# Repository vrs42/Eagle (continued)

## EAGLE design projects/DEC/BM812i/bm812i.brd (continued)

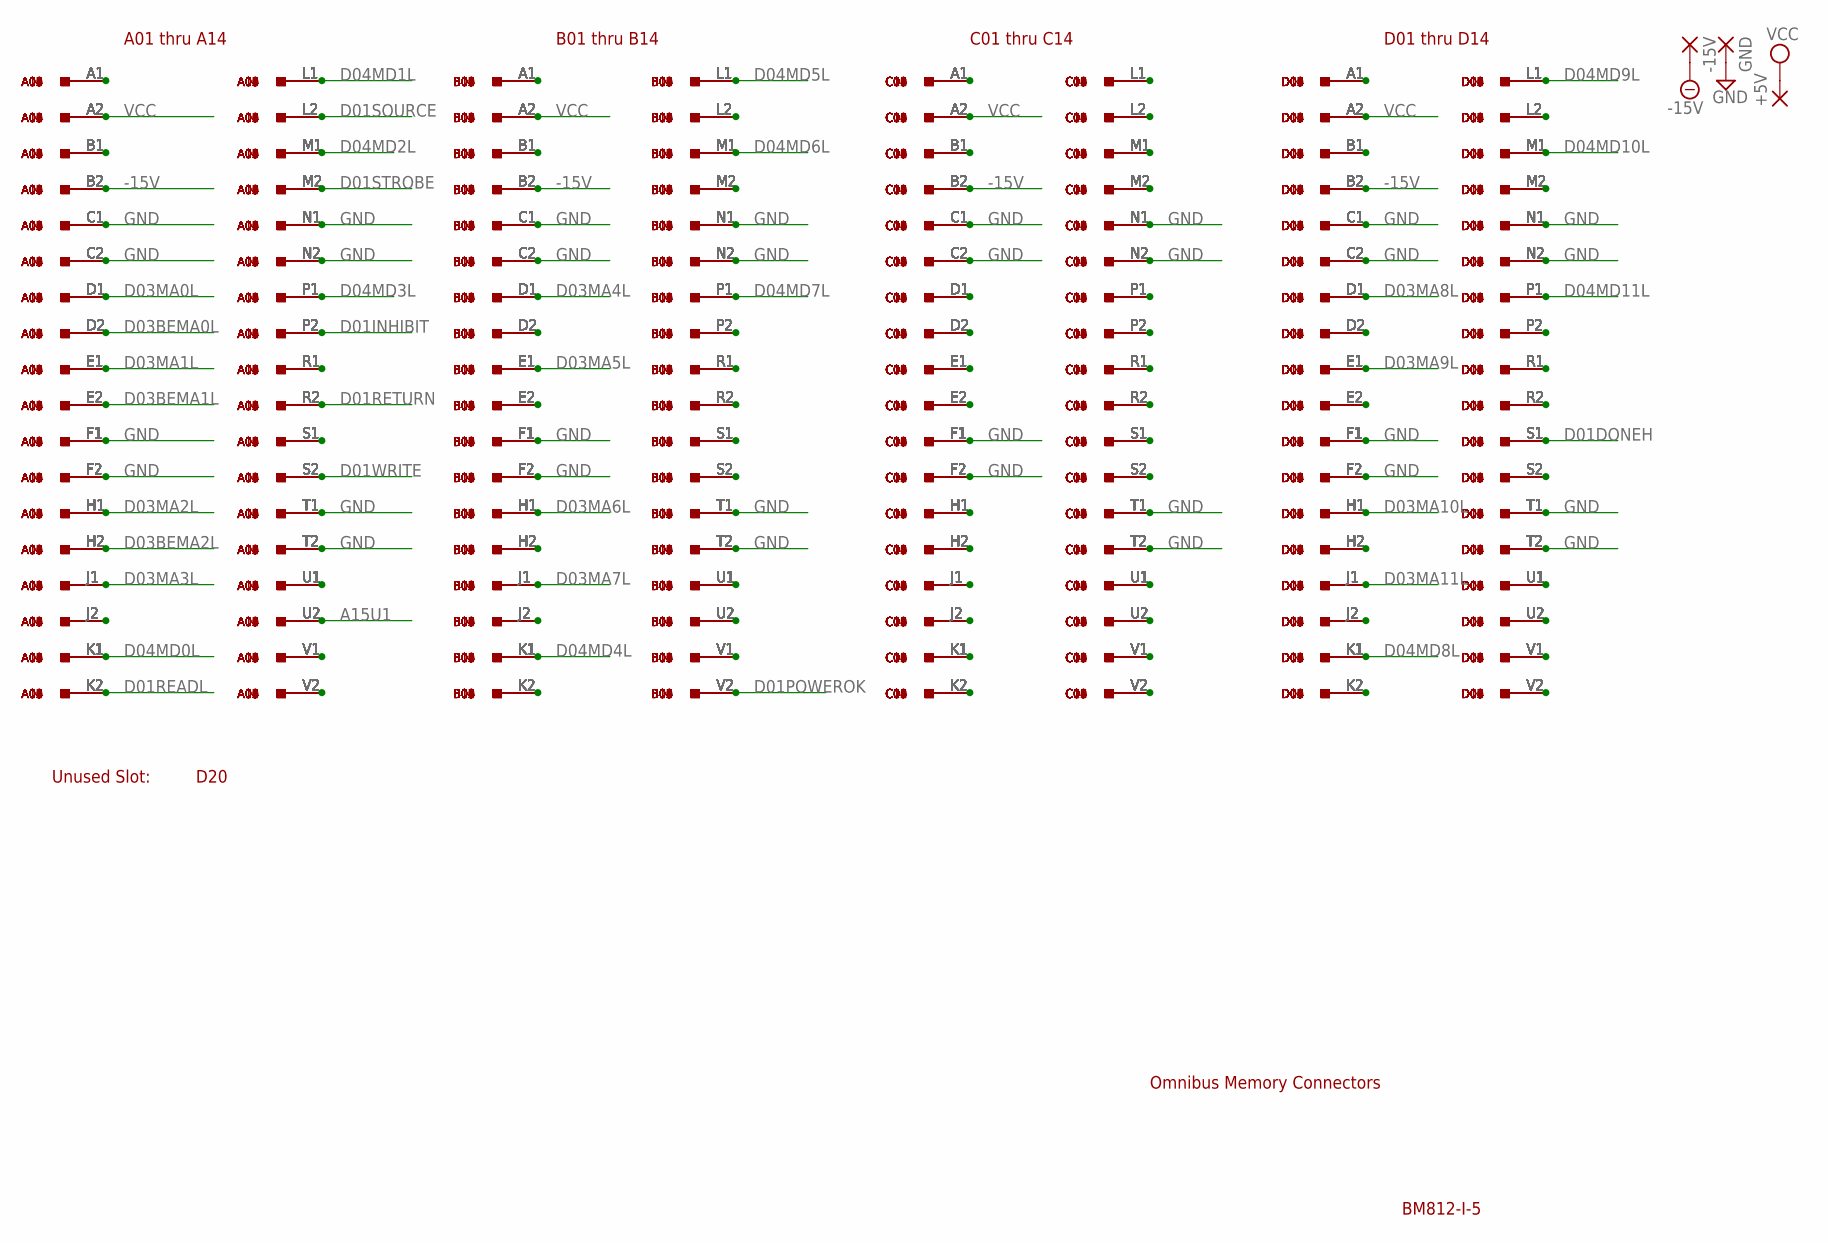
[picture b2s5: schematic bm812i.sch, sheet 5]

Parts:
+5V: 2,54/0,8
-15V: 2,54/0,8
A01, A02, A03, A04, A05, A06, A07, A08, A09, A10, A11, A12, A13, A14: M916; H807
B01, B02, B03, B04, B05, B06, B07, B08, B09, B10, B11, B12, B13, B14: M916; H807
C01, C02, C03, C04, C05, C06, C07, C08, C09, C10, C11, C12, C13, C14: M916; H807
D01, D02, D03, D04, D05, D06, D07, D08, D09, D10, D11, D12, D13, D14: M916; H807
D20: H807
GND: 2,54/0,8

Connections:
-15V: -15V.1, A01.B2, A02.B2, A03.B2, A04.B2, A05.B2, A06.B2, A07.B2, A08.B2, A09.B2, A10.B2, A11.B2, A12.B2, A13.B2, A14.B2, B01.B2, B02.B2, B03.B2, B04.B2, B05.B2, B06.B2, B07.B2, B08.B2, B09.B2, B10.B2, B11.B2, B12.B2, B13.B2, B14.B2, C01.B2, C02.B2, C03.B2, C04.B2, C05.B2, C06.B2, C07.B2, C08.B2, C09.B2, C10.B2, C11.B2, C12.B2, C13.B2, C14.B2, D01.B2, D02.B2, D03.B2, D04.B2, D05.B2, D06.B2, D07.B2, D08.B2, D09.B2, D10.B2, D11.B2, D12.B2, D13.B2, D14.B2
A15U1: A01.U2, A02.U2, A03.U2, A04.U2, A05.U2, A06.U2, A07.U2, A08.U2, A09.U2, A10.U2, A11.U2, A12.U2, A13.U2, A14.U2; also elsewhere on the board
D01DONEH: D01.S1, D02.S1, D03.S1, D04.S1, D05.S1, D06.S1, D07.S1, D08.S1, D09.S1, D10.S1, D11.S1, D12.S1, D13.S1, D14.S1; also elsewhere on the board
D01INHIBIT: A01.P2, A02.P2, A03.P2, A04.P2, A05.P2, A06.P2, A07.P2, A08.P2, A09.P2, A10.P2, A11.P2, A12.P2, A13.P2, A14.P2; also elsewhere on the board
D01POWEROK: B01.V2, B02.V2, B03.V2, B04.V2, B05.V2, B06.V2, B07.V2, B08.V2, B09.V2, B10.V2, B11.V2, B12.V2, B13.V2, B14.V2; also elsewhere on the board
D01READL: A01.K2, A02.K2, A03.K2, A04.K2, A05.K2, A06.K2, A07.K2, A08.K2, A09.K2, A10.K2, A11.K2, A12.K2, A13.K2, A14.K2; also elsewhere on the board
D01RETURN: A01.R2, A02.R2, A03.R2, A04.R2, A05.R2, A06.R2, A07.R2, A08.R2, A09.R2, A10.R2, A11.R2, A12.R2, A13.R2, A14.R2; also elsewhere on the board
D01SOURCE: A01.L2, A02.L2, A03.L2, A04.L2, A05.L2, A06.L2, A07.L2, A08.L2, A09.L2, A10.L2, A11.L2, A12.L2, A13.L2, A14.L2; also elsewhere on the board
D01STROBE: A01.M2, A02.M2, A03.M2, A04.M2, A05.M2, A06.M2, A07.M2, A08.M2, A09.M2, A10.M2, A11.M2, A12.M2, A13.M2, A14.M2; also elsewhere on the board
D01WRITE: A01.S2, A02.S2, A03.S2, A04.S2, A05.S2, A06.S2, A07.S2, A08.S2, A09.S2, A10.S2, A11.S2, A12.S2, A13.S2, A14.S2; also elsewhere on the board
D03BEMA0L: A01.D2, A02.D2, A03.D2, A04.D2, A05.D2, A06.D2, A07.D2, A08.D2, A09.D2, A10.D2, A11.D2, A12.D2, A13.D2, A14.D2; also elsewhere on the board
D03BEMA1L: A01.E2, A02.E2, A03.E2, A04.E2, A05.E2, A06.E2, A07.E2, A08.E2, A09.E2, A10.E2, A11.E2, A12.E2, A13.E2, A14.E2; also elsewhere on the board
D03BEMA2L: A01.H2, A02.H2, A03.H2, A04.H2, A05.H2, A06.H2, A07.H2, A08.H2, A09.H2, A10.H2, A11.H2, A12.H2, A13.H2, A14.H2; also elsewhere on the board
D03MA0L: A01.D1, A02.D1, A03.D1, A04.D1, A05.D1, A06.D1, A07.D1, A08.D1, A09.D1, A10.D1, A11.D1, A12.D1, A13.D1, A14.D1; also elsewhere on the board
D03MA1L: A01.E1, A02.E1, A03.E1, A04.E1, A05.E1, A06.E1, A07.E1, A08.E1, A09.E1, A10.E1, A11.E1, A12.E1, A13.E1, A14.E1; also elsewhere on the board
D03MA2L: A01.H1, A02.H1, A03.H1, A04.H1, A05.H1, A06.H1, A07.H1, A08.H1, A09.H1, A10.H1, A11.H1, A12.H1, A13.H1, A14.H1; also elsewhere on the board
D03MA3L: A01.J1, A02.J1, A03.J1, A04.J1, A05.J1, A06.J1, A07.J1, A08.J1, A09.J1, A10.J1, A11.J1, A12.J1, A13.J1, A14.J1; also elsewhere on the board
D03MA4L: B01.D1, B02.D1, B03.D1, B04.D1, B05.D1, B06.D1, B07.D1, B08.D1, B09.D1, B10.D1, B11.D1, B12.D1, B13.D1, B14.D1; also elsewhere on the board
D03MA5L: B01.E1, B02.E1, B03.E1, B04.E1, B05.E1, B06.E1, B07.E1, B08.E1, B09.E1, B10.E1, B11.E1, B12.E1, B13.E1, B14.E1; also elsewhere on the board
D03MA6L: B01.H1, B02.H1, B03.H1, B04.H1, B05.H1, B06.H1, B07.H1, B08.H1, B09.H1, B10.H1, B11.H1, B12.H1, B13.H1, B14.H1; also elsewhere on the board
D03MA7L: B01.J1, B02.J1, B03.J1, B04.J1, B05.J1, B06.J1, B07.J1, B08.J1, B09.J1, B10.J1, B11.J1, B12.J1, B13.J1, B14.J1; also elsewhere on the board
D03MA8L: D01.D1, D02.D1, D03.D1, D04.D1, D05.D1, D06.D1, D07.D1, D08.D1, D09.D1, D10.D1, D11.D1, D12.D1, D13.D1, D14.D1; also elsewhere on the board
D03MA9L: D01.E1, D02.E1, D03.E1, D04.E1, D05.E1, D06.E1, D07.E1, D08.E1, D09.E1, D10.E1, D11.E1, D12.E1, D13.E1, D14.E1; also elsewhere on the board
D03MA10L: D01.H1, D02.H1, D03.H1, D04.H1, D05.H1, D06.H1, D07.H1, D08.H1, D09.H1, D10.H1, D11.H1, D12.H1, D13.H1, D14.H1; also elsewhere on the board
D03MA11L: D01.J1, D02.J1, D03.J1, D04.J1, D05.J1, D06.J1, D07.J1, D08.J1, D09.J1, D10.J1, D11.J1, D12.J1, D13.J1, D14.J1; also elsewhere on the board
D04MD0L: A01.K1, A02.K1, A03.K1, A04.K1, A05.K1, A06.K1, A07.K1, A08.K1, A09.K1, A10.K1, A11.K1, A12.K1, A13.K1, A14.K1; also elsewhere on the board
D04MD1L: A01.L1, A02.L1, A03.L1, A04.L1, A05.L1, A06.L1, A07.L1, A08.L1, A09.L1, A10.L1, A11.L1, A12.L1, A13.L1, A14.L1; also elsewhere on the board
D04MD2L: A01.M1, A02.M1, A03.M1, A04.M1, A05.M1, A06.M1, A07.M1, A08.M1, A09.M1, A10.M1, A11.M1, A12.M1, A13.M1, A14.M1; also elsewhere on the board
D04MD3L: A01.P1, A02.P1, A03.P1, A04.P1, A05.P1, A06.P1, A07.P1, A08.P1, A09.P1, A10.P1, A11.P1, A12.P1, A13.P1, A14.P1; also elsewhere on the board
D04MD4L: B01.K1, B02.K1, B03.K1, B04.K1, B05.K1, B06.K1, B07.K1, B08.K1, B09.K1, B10.K1, B11.K1, B12.K1, B13.K1, B14.K1; also elsewhere on the board
D04MD5L: B01.L1, B02.L1, B03.L1, B04.L1, B05.L1, B06.L1, B07.L1, B08.L1, B09.L1, B10.L1, B11.L1, B12.L1, B13.L1, B14.L1; also elsewhere on the board
D04MD6L: B01.M1, B02.M1, B03.M1, B04.M1, B05.M1, B06.M1, B07.M1, B08.M1, B09.M1, B10.M1, B11.M1, B12.M1, B13.M1, B14.M1; also elsewhere on the board
D04MD7L: B01.P1, B02.P1, B03.P1, B04.P1, B05.P1, B06.P1, B07.P1, B08.P1, B09.P1, B10.P1, B11.P1, B12.P1, B13.P1, B14.P1; also elsewhere on the board
D04MD8L: D01.K1, D02.K1, D03.K1, D04.K1, D05.K1, D06.K1, D07.K1, D08.K1, D09.K1, D10.K1, D11.K1, D12.K1, D13.K1, D14.K1; also elsewhere on the board
D04MD9L: D01.L1, D02.L1, D03.L1, D04.L1, D05.L1, D06.L1, D07.L1, D08.L1, D09.L1, D10.L1, D11.L1, D12.L1, D13.L1, D14.L1; also elsewhere on the board
D04MD10L: D01.M1, D02.M1, D03.M1, D04.M1, D05.M1, D06.M1, D07.M1, D08.M1, D09.M1, D10.M1, D11.M1, D12.M1, D13.M1, D14.M1; also elsewhere on the board
D04MD11L: D01.P1, D02.P1, D03.P1, D04.P1, D05.P1, D06.P1, D07.P1, D08.P1, D09.P1, D10.P1, D11.P1, D12.P1, D13.P1, D14.P1; also elsewhere on the board
GND: A01.C1, A01.C2, A01.F1, A01.F2, A01.N1, A01.N2, A01.T1, A01.T2, A02.C1, A02.C2, A02.F1, A02.F2, A02.N1, A02.N2, A02.T1, A02.T2, A03.C1, A03.C2, A03.F1, A03.F2, A03.N1, A03.N2, A03.T1, A03.T2, A04.C1, A04.C2, A04.F1, A04.F2, A04.N1, A04.N2, A04.T1, A04.T2, A05.C1, A05.C2, A05.F1, A05.F2, A05.N1, A05.N2, A05.T1, A05.T2, A06.C1, A06.C2, A06.F1, A06.F2, A06.N1, A06.N2, A06.T1, A06.T2, A07.C1, A07.C2, A07.F1, A07.F2, A07.N1, A07.N2, A07.T1, A07.T2, A08.C1, A08.C2, A08.F1, A08.F2, A08.N1, A08.N2, A08.T1, A08.T2, A09.C1, A09.C2, A09.F1, A09.F2, A09.N1, A09.N2, A09.T1, A09.T2, A10.C1, A10.C2, A10.F1, A10.F2, A10.N1, A10.N2, A10.T1, A10.T2, A11.C1, A11.C2, A11.F1, A11.F2, A11.N1, A11.N2, A11.T1, A11.T2, A12.C1, A12.C2, A12.F1, A12.F2, A12.N1, A12.N2, A12.T1, A12.T2, A13.C1, A13.C2, A13.F1, A13.F2, A13.N1, A13.N2, A13.T1, A13.T2, A14.C1, A14.C2, A14.F1, A14.F2, A14.N1, A14.N2, A14.T1, A14.T2, B01.C1, B01.C2, B01.F1, B01.F2, B01.N1, B01.N2, B01.T1, B01.T2, B02.C1, B02.C2, B02.F1, B02.F2, B02.N1, B02.N2, B02.T1, B02.T2, B03.C1, B03.C2, B03.F1, B03.F2, B03.N1, B03.N2, B03.T1, B03.T2, B04.C1, B04.C2, B04.F1, B04.F2, B04.N1, B04.N2, B04.T1, B04.T2, B05.C1, B05.C2, B05.F1, B05.F2, B05.N1, B05.N2, B05.T1, B05.T2, B06.C1, B06.C2, B06.F1, B06.F2, B06.N1, B06.N2, B06.T1, B06.T2, B07.C1, B07.C2, B07.F1, B07.F2, B07.N1, B07.N2, B07.T1, B07.T2, B08.C1, B08.C2, B08.F1, B08.F2, B08.N1, B08.N2, B08.T1, B08.T2, B09.C1, B09.C2, B09.F1, B09.F2, B09.N1, B09.N2, B09.T1, B09.T2, B10.C1, B10.C2, B10.F1, B10.F2, B10.N1, B10.N2, B10.T1, B10.T2, B11.C1, B11.C2, B11.F1, B11.F2, B11.N1, B11.N2, B11.T1, B11.T2, B12.C1, B12.C2, B12.F1, B12.F2, B12.N1, B12.N2, B12.T1, B12.T2, B13.C1, B13.C2, B13.F1, B13.F2, B13.N1, B13.N2, B13.T1, B13.T2, B14.C1, B14.C2, B14.F1, B14.F2, B14.N1, B14.N2, B14.T1, B14.T2, C01.C1, C01.C2, C01.F1, C01.F2, C01.N1, C01.N2, C01.T1, C01.T2, C02.C1, C02.C2, C02.F1, C02.F2, C02.N1, C02.N2, C02.T1, C02.T2, C03.C1, C03.C2, C03.F1, C03.F2, C03.N1, C03.N2, C03.T1, C03.T2, C04.C1, C04.C2, C04.F1, C04.F2, C04.N1, C04.N2, C04.T1, C04.T2, C05.C1, C05.C2, C05.F1, C05.F2, C05.N1, C05.N2, C05.T1, C05.T2, C06.C1, C06.C2, C06.F1, C06.F2, C06.N1, C06.N2, C06.T1, C06.T2, C07.C1, C07.C2, C07.F1, C07.F2, C07.N1, C07.N2, C07.T1, C07.T2, C08.C1, C08.C2, C08.F1, C08.F2, C08.N1, C08.N2, C08.T1, C08.T2, C09.C1, C09.C2, C09.F1, C09.F2, C09.N1, C09.N2, C09.T1, C09.T2, C10.C1, C10.C2, C10.F1, C10.F2, C10.N1, C10.N2, C10.T1, C10.T2, C11.C1, C11.C2, C11.F1, C11.F2, C11.N1, C11.N2, C11.T1, C11.T2, C12.C1, C12.C2, C12.F1, C12.F2, C12.N1, C12.N2, C12.T1, C12.T2, C13.C1, C13.C2, C13.F1, C13.F2, C13.N1, C13.N2, C13.T1, C13.T2, C14.C1, C14.C2, C14.F1, C14.F2, C14.N1, C14.N2, C14.T1, C14.T2, D01.C1, D01.C2, D01.F1, D01.F2, D01.N1, D01.N2, D01.T1, D01.T2, D02.C1, D02.C2, D02.F1, D02.F2, D02.N1, D02.N2, D02.T1, D02.T2, D03.C1, D03.C2, D03.F1, D03.F2, D03.N1, D03.N2, D03.T1, D03.T2, D04.C1, D04.C2, D04.F1, D04.F2, D04.N1, D04.N2, D04.T1, D04.T2, D05.C1, D05.C2, D05.F1, D05.F2, D05.N1, D05.N2, D05.T1, D05.T2, D06.C1, D06.C2, D06.F1, D06.F2, D06.N1, D06.N2, D06.T1, D06.T2, D07.C1, D07.C2, D07.F1, D07.F2, D07.N1, D07.N2, D07.T1, D07.T2, D08.C1, D08.C2, D08.F1, D08.F2, D08.N1, D08.N2, D08.T1, D08.T2, D09.C1, D09.C2, D09.F1, D09.F2, D09.N1, D09.N2, D09.T1, D09.T2, D10.C1, D10.C2, D10.F1, D10.F2, D10.N1, D10.N2, D10.T1, D10.T2, D11.C1, D11.C2, D11.F1, D11.F2, D11.N1, D11.N2, D11.T1, D11.T2, D12.C1, D12.C2, D12.F1, D12.F2, D12.N1, D12.N2, D12.T1, D12.T2, D13.C1, D13.C2, D13.F1, D13.F2, D13.N1, D13.N2, D13.T1, D13.T2, D14.C1, D14.C2, D14.F1, D14.F2, D14.N1, D14.N2, D14.T1, D14.T2, GND.1; also elsewhere on the board
unnamed: A01.A1, A02.A1, A03.A1, A04.A1, A05.A1, A06.A1, A07.A1, A08.A1, A09.A1, A10.A1, A11.A1, A12.A1, A13.A1, A14.A1
unnamed: A01.B1, A02.B1, A03.B1, A04.B1, A05.B1, A06.B1, A07.B1, A08.B1, A09.B1, A10.B1, A11.B1, A12.B1, A13.B1, A14.B1
unnamed: A01.J2, A02.J2, A03.J2, A04.J2, A05.J2, A06.J2, A07.J2, A08.J2, A09.J2, A10.J2, A11.J2, A12.J2, A13.J2, A14.J2
unnamed: A01.R1, A02.R1, A03.R1, A04.R1, A05.R1, A06.R1, A07.R1, A08.R1, A09.R1, A10.R1, A11.R1, A12.R1, A13.R1, A14.R1
unnamed: A01.S1, A02.S1, A03.S1, A04.S1, A05.S1, A06.S1, A07.S1, A08.S1, A09.S1, A10.S1, A11.S1, A12.S1, A13.S1, A14.S1
unnamed: A01.U1, A02.U1, A03.U1, A04.U1, A05.U1, A06.U1, A07.U1, A08.U1, A09.U1, A10.U1, A11.U1, A12.U1, A13.U1, A14.U1
unnamed: A01.V1, A02.V1, A03.V1, A04.V1, A05.V1, A06.V1, A07.V1, A08.V1, A09.V1, A10.V1, A11.V1, A12.V1, A13.V1, A14.V1
unnamed: A01.V2, A02.V2, A03.V2, A04.V2, A05.V2, A06.V2, A07.V2, A08.V2, A09.V2, A10.V2, A11.V2, A12.V2, A13.V2, A14.V2
unnamed: B01.A1, B02.A1, B03.A1, B04.A1, B05.A1, B06.A1, B07.A1, B08.A1, B09.A1, B10.A1, B11.A1, B12.A1, B13.A1, B14.A1
unnamed: B01.B1, B02.B1, B03.B1, B04.B1, B05.B1, B06.B1, B07.B1, B08.B1, B09.B1, B10.B1, B11.B1, B12.B1, B13.B1, B14.B1
unnamed: B01.D2, B02.D2, B03.D2, B04.D2, B05.D2, B06.D2, B07.D2, B08.D2, B09.D2, B10.D2, B11.D2, B12.D2, B13.D2, B14.D2
unnamed: B01.E2, B02.E2, B03.E2, B04.E2, B05.E2, B06.E2, B07.E2, B08.E2, B09.E2, B10.E2, B11.E2, B12.E2, B13.E2, B14.E2
unnamed: B01.H2, B02.H2, B03.H2, B04.H2, B05.H2, B06.H2, B07.H2, B08.H2, B09.H2, B10.H2, B11.H2, B12.H2, B13.H2, B14.H2
unnamed: B01.J2, B02.J2, B03.J2, B04.J2, B05.J2, B06.J2, B07.J2, B08.J2, B09.J2, B10.J2, B11.J2, B12.J2, B13.J2, B14.J2
unnamed: B01.K2, B02.K2, B03.K2, B04.K2, B05.K2, B06.K2, B07.K2, B08.K2, B09.K2, B10.K2, B11.K2, B12.K2, B13.K2, B14.K2
unnamed: B01.L2, B02.L2, B03.L2, B04.L2, B05.L2, B06.L2, B07.L2, B08.L2, B09.L2, B10.L2, B11.L2, B12.L2, B13.L2, B14.L2
unnamed: B01.M2, B02.M2, B03.M2, B04.M2, B05.M2, B06.M2, B07.M2, B08.M2, B09.M2, B10.M2, B11.M2, B12.M2, B13.M2, B14.M2
unnamed: B01.P2, B02.P2, B03.P2, B04.P2, B05.P2, B06.P2, B07.P2, B08.P2, B09.P2, B10.P2, B11.P2, B12.P2, B13.P2, B14.P2
unnamed: B01.R1, B02.R1, B03.R1, B04.R1, B05.R1, B06.R1, B07.R1, B08.R1, B09.R1, B10.R1, B11.R1, B12.R1, B13.R1, B14.R1
unnamed: B01.R2, B02.R2, B03.R2, B04.R2, B05.R2, B06.R2, B07.R2, B08.R2, B09.R2, B10.R2, B11.R2, B12.R2, B13.R2, B14.R2
unnamed: B01.S1, B02.S1, B03.S1, B04.S1, B05.S1, B06.S1, B07.S1, B08.S1, B09.S1, B10.S1, B11.S1, B12.S1, B13.S1, B14.S1
unnamed: B01.S2, B02.S2, B03.S2, B04.S2, B05.S2, B06.S2, B07.S2, B08.S2, B09.S2, B10.S2, B11.S2, B12.S2, B13.S2, B14.S2
unnamed: B01.U1, B02.U1, B03.U1, B04.U1, B05.U1, B06.U1, B07.U1, B08.U1, B09.U1, B10.U1, B11.U1, B12.U1, B13.U1, B14.U1
unnamed: B01.U2, B02.U2, B03.U2, B04.U2, B05.U2, B06.U2, B07.U2, B08.U2, B09.U2, B10.U2, B11.U2, B12.U2, B13.U2, B14.U2
unnamed: B01.V1, B02.V1, B03.V1, B04.V1, B05.V1, B06.V1, B07.V1, B08.V1, B09.V1, B10.V1, B11.V1, B12.V1, B13.V1, B14.V1
unnamed: C01.A1, C02.A1, C03.A1, C04.A1, C05.A1, C06.A1, C07.A1, C08.A1, C09.A1, C10.A1, C11.A1, C12.A1, C13.A1, C14.A1
unnamed: C01.B1, C02.B1, C03.B1, C04.B1, C05.B1, C06.B1, C07.B1, C08.B1, C09.B1, C10.B1, C11.B1, C12.B1, C13.B1, C14.B1
unnamed: C01.D1, C02.D1, C03.D1, C04.D1, C05.D1, C06.D1, C07.D1, C08.D1, C09.D1, C10.D1, C11.D1, C12.D1, C13.D1, C14.D1
unnamed: C01.D2, C02.D2, C03.D2, C04.D2, C05.D2, C06.D2, C07.D2, C08.D2, C09.D2, C10.D2, C11.D2, C12.D2, C13.D2, C14.D2
unnamed: C01.E1, C02.E1, C03.E1, C04.E1, C05.E1, C06.E1, C07.E1, C08.E1, C09.E1, C10.E1, C11.E1, C12.E1, C13.E1, C14.E1
unnamed: C01.E2, C02.E2, C03.E2, C04.E2, C05.E2, C06.E2, C07.E2, C08.E2, C09.E2, C10.E2, C11.E2, C12.E2, C13.E2, C14.E2
unnamed: C01.H1, C02.H1, C03.H1, C04.H1, C05.H1, C06.H1, C07.H1, C08.H1, C09.H1, C10.H1, C11.H1, C12.H1, C13.H1, C14.H1
unnamed: C01.H2, C02.H2, C03.H2, C04.H2, C05.H2, C06.H2, C07.H2, C08.H2, C09.H2, C10.H2, C11.H2, C12.H2, C13.H2, C14.H2
unnamed: C01.J1, C02.J1, C03.J1, C04.J1, C05.J1, C06.J1, C07.J1, C08.J1, C09.J1, C10.J1, C11.J1, C12.J1, C13.J1, C14.J1
unnamed: C01.J2, C02.J2, C03.J2, C04.J2, C05.J2, C06.J2, C07.J2, C08.J2, C09.J2, C10.J2, C11.J2, C12.J2, C13.J2, C14.J2
unnamed: C01.K1, C02.K1, C03.K1, C04.K1, C05.K1, C06.K1, C07.K1, C08.K1, C09.K1, C10.K1, C11.K1, C12.K1, C13.K1, C14.K1
unnamed: C01.K2, C02.K2, C03.K2, C04.K2, C05.K2, C06.K2, C07.K2, C08.K2, C09.K2, C10.K2, C11.K2, C12.K2, C13.K2, C14.K2
unnamed: C01.L1, C02.L1, C03.L1, C04.L1, C05.L1, C06.L1, C07.L1, C08.L1, C09.L1, C10.L1, C11.L1, C12.L1, C13.L1, C14.L1
unnamed: C01.L2, C02.L2, C03.L2, C04.L2, C05.L2, C06.L2, C07.L2, C08.L2, C09.L2, C10.L2, C11.L2, C12.L2, C13.L2, C14.L2
unnamed: C01.M1, C02.M1, C03.M1, C04.M1, C05.M1, C06.M1, C07.M1, C08.M1, C09.M1, C10.M1, C11.M1, C12.M1, C13.M1, C14.M1
unnamed: C01.M2, C02.M2, C03.M2, C04.M2, C05.M2, C06.M2, C07.M2, C08.M2, C09.M2, C10.M2, C11.M2, C12.M2, C13.M2, C14.M2
unnamed: C01.P1, C02.P1, C03.P1, C04.P1, C05.P1, C06.P1, C07.P1, C08.P1, C09.P1, C10.P1, C11.P1, C12.P1, C13.P1, C14.P1
unnamed: C01.P2, C02.P2, C03.P2, C04.P2, C05.P2, C06.P2, C07.P2, C08.P2, C09.P2, C10.P2, C11.P2, C12.P2, C13.P2, C14.P2
unnamed: C01.R1, C02.R1, C03.R1, C04.R1, C05.R1, C06.R1, C07.R1, C08.R1, C09.R1, C10.R1, C11.R1, C12.R1, C13.R1, C14.R1
unnamed: C01.R2, C02.R2, C03.R2, C04.R2, C05.R2, C06.R2, C07.R2, C08.R2, C09.R2, C10.R2, C11.R2, C12.R2, C13.R2, C14.R2
unnamed: C01.S1, C02.S1, C03.S1, C04.S1, C05.S1, C06.S1, C07.S1, C08.S1, C09.S1, C10.S1, C11.S1, C12.S1, C13.S1, C14.S1
unnamed: C01.S2, C02.S2, C03.S2, C04.S2, C05.S2, C06.S2, C07.S2, C08.S2, C09.S2, C10.S2, C11.S2, C12.S2, C13.S2, C14.S2
unnamed: C01.U1, C02.U1, C03.U1, C04.U1, C05.U1, C06.U1, C07.U1, C08.U1, C09.U1, C10.U1, C11.U1, C12.U1, C13.U1, C14.U1
unnamed: C01.U2, C02.U2, C03.U2, C04.U2, C05.U2, C06.U2, C07.U2, C08.U2, C09.U2, C10.U2, C11.U2, C12.U2, C13.U2, C14.U2
unnamed: C01.V1, C02.V1, C03.V1, C04.V1, C05.V1, C06.V1, C07.V1, C08.V1, C09.V1, C10.V1, C11.V1, C12.V1, C13.V1, C14.V1
unnamed: C01.V2, C02.V2, C03.V2, C04.V2, C05.V2, C06.V2, C07.V2, C08.V2, C09.V2, C10.V2, C11.V2, C12.V2, C13.V2, C14.V2
unnamed: D01.A1, D02.A1, D03.A1, D04.A1, D05.A1, D06.A1, D07.A1, D08.A1, D09.A1, D10.A1, D11.A1, D12.A1, D13.A1, D14.A1
unnamed: D01.B1, D02.B1, D03.B1, D04.B1, D05.B1, D06.B1, D07.B1, D08.B1, D09.B1, D10.B1, D11.B1, D12.B1, D13.B1, D14.B1
unnamed: D01.D2, D02.D2, D03.D2, D04.D2, D05.D2, D06.D2, D07.D2, D08.D2, D09.D2, D10.D2, D11.D2, D12.D2, D13.D2, D14.D2
unnamed: D01.E2, D02.E2, D03.E2, D04.E2, D05.E2, D06.E2, D07.E2, D08.E2, D09.E2, D10.E2, D11.E2, D12.E2, D13.E2, D14.E2
unnamed: D01.H2, D02.H2, D03.H2, D04.H2, D05.H2, D06.H2, D07.H2, D08.H2, D09.H2, D10.H2, D11.H2, D12.H2, D13.H2, D14.H2
unnamed: D01.J2, D02.J2, D03.J2, D04.J2, D05.J2, D06.J2, D07.J2, D08.J2, D09.J2, D10.J2, D11.J2, D12.J2, D13.J2, D14.J2
unnamed: D01.K2, D02.K2, D03.K2, D04.K2, D05.K2, D06.K2, D07.K2, D08.K2, D09.K2, D10.K2, D11.K2, D12.K2, D13.K2, D14.K2
unnamed: D01.L2, D02.L2, D03.L2, D04.L2, D05.L2, D06.L2, D07.L2, D08.L2, D09.L2, D10.L2, D11.L2, D12.L2, D13.L2, D14.L2
unnamed: D01.M2, D02.M2, D03.M2, D04.M2, D05.M2, D06.M2, D07.M2, D08.M2, D09.M2, D10.M2, D11.M2, D12.M2, D13.M2, D14.M2
unnamed: D01.P2, D02.P2, D03.P2, D04.P2, D05.P2, D06.P2, D07.P2, D08.P2, D09.P2, D10.P2, D11.P2, D12.P2, D13.P2, D14.P2
unnamed: D01.R1, D02.R1, D03.R1, D04.R1, D05.R1, D06.R1, D07.R1, D08.R1, D09.R1, D10.R1, D11.R1, D12.R1, D13.R1, D14.R1
unnamed: D01.R2, D02.R2, D03.R2, D04.R2, D05.R2, D06.R2, D07.R2, D08.R2, D09.R2, D10.R2, D11.R2, D12.R2, D13.R2, D14.R2
unnamed: D01.S2, D02.S2, D03.S2, D04.S2, D05.S2, D06.S2, D07.S2, D08.S2, D09.S2, D10.S2, D11.S2, D12.S2, D13.S2, D14.S2
unnamed: D01.U1, D02.U1, D03.U1, D04.U1, D05.U1, D06.U1, D07.U1, D08.U1, D09.U1, D10.U1, D11.U1, D12.U1, D13.U1, D14.U1
unnamed: D01.U2, D02.U2, D03.U2, D04.U2, D05.U2, D06.U2, D07.U2, D08.U2, D09.U2, D10.U2, D11.U2, D12.U2, D13.U2, D14.U2
unnamed: D01.V1, D02.V1, D03.V1, D04.V1, D05.V1, D06.V1, D07.V1, D08.V1, D09.V1, D10.V1, D11.V1, D12.V1, D13.V1, D14.V1
unnamed: D01.V2, D02.V2, D03.V2, D04.V2, D05.V2, D06.V2, D07.V2, D08.V2, D09.V2, D10.V2, D11.V2, D12.V2, D13.V2, D14.V2
VCC: +5V.1, A01.A2, A02.A2, A03.A2, A04.A2, A05.A2, A06.A2, A07.A2, A08.A2, A09.A2, A10.A2, A11.A2, A12.A2, A13.A2, A14.A2, B01.A2, B02.A2, B03.A2, B04.A2, B05.A2, B06.A2, B07.A2, B08.A2, B09.A2, B10.A2, B11.A2, B12.A2, B13.A2, B14.A2, C01.A2, C02.A2, C03.A2, C04.A2, C05.A2, C06.A2, C07.A2, C08.A2, C09.A2, C10.A2, C11.A2, C12.A2, C13.A2, C14.A2, D01.A2, D02.A2, D03.A2, D04.A2, D05.A2, D06.A2, D07.A2, D08.A2, D09.A2, D10.A2, D11.A2, D12.A2, D13.A2, D14.A2; also elsewhere on the board

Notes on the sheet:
Unused Slot:
Omnibus Memory Connectors
BM812-I-5
A01 thru A14
B01 thru B14
C01 thru C14
D01 thru D14

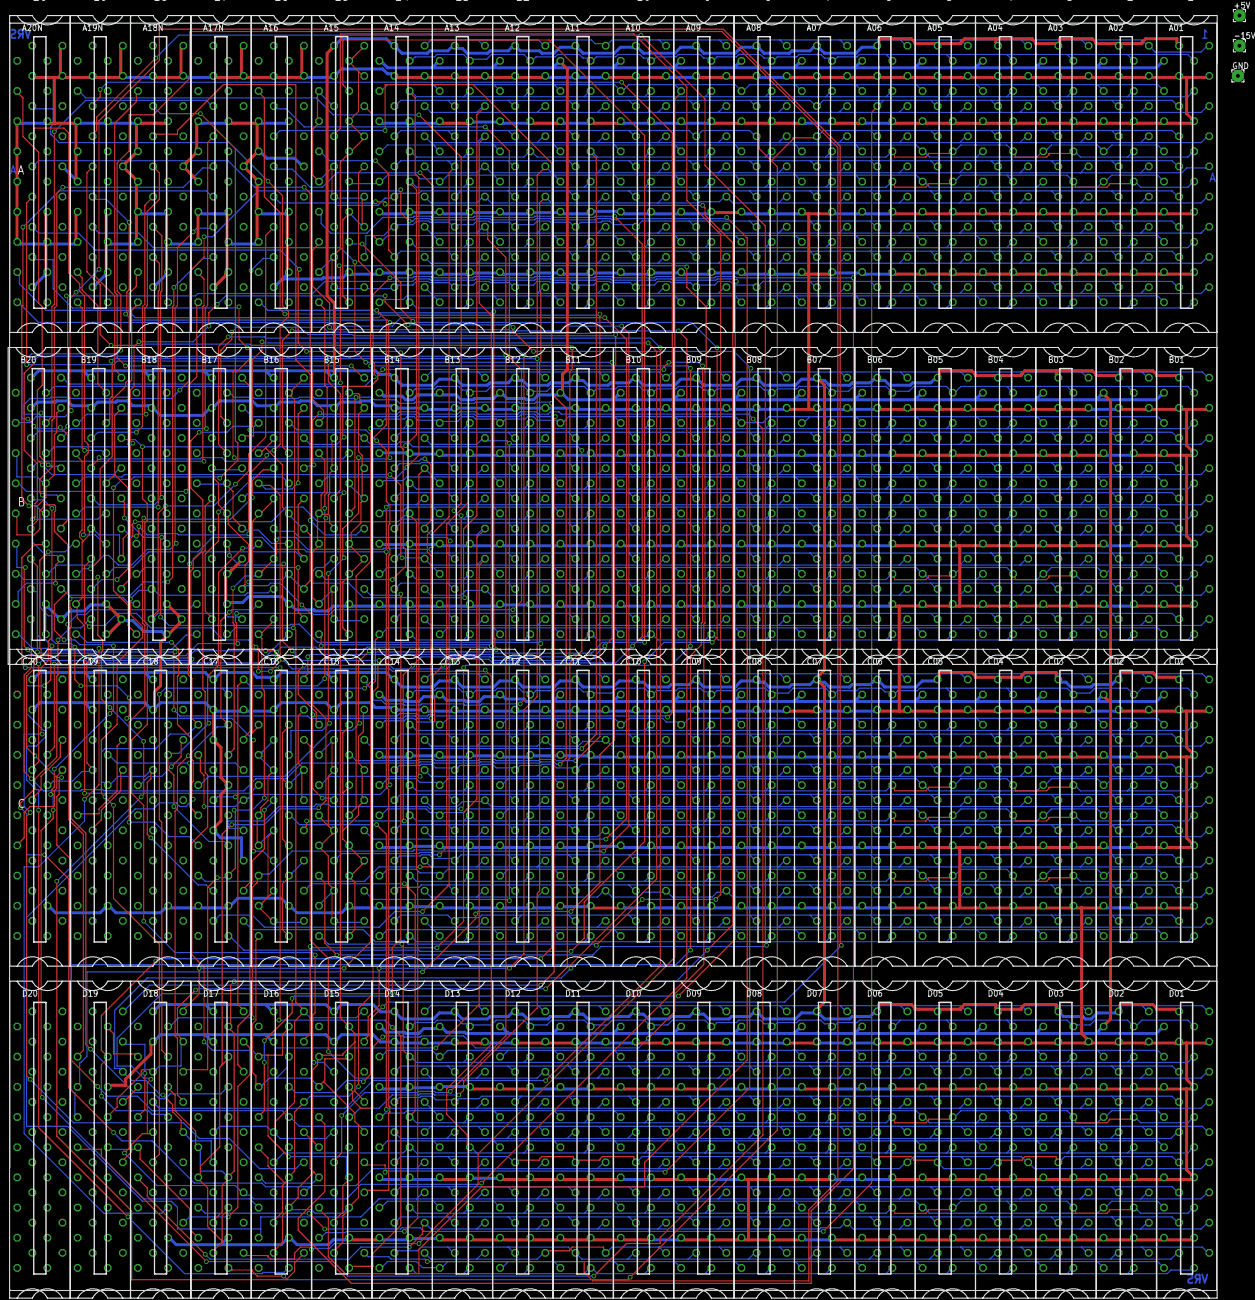
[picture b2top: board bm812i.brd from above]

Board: 4 copper layers, 254.1 x 266.7 mm, 83 parts (0 on the bottom side), 224 nets.

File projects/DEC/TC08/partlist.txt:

Partlist

Exported from tc08.sch at  8/08/2006 10:36:56a

EAGLE Version 4.11 Copyright (c) 1988-2003 CadSoft

Part     Value          Device     Package  Library  Sheet

A02      M903           M903       H807     dec-m    12
A03      M903           M903       H807     dec-m    12
A04      M903           M903       H807     dec-m    12
A05      M903           M903       H807     dec-m    12
A06      M903           M903       H807     dec-m    12
A07      M161           M161       H807     dec-m    2
A08      M206           M206X      H807     dec-m    4
A09      M117           M117       H807     dec-m    2
A10      M113           M113       H807     dec-m    2
A11      M111           M111       H807     dec-m    1
A12      M113           M113       H807     dec-m    1
A14      M302           M302       H807     dec-m    3
A15      M627           M627       H807     dec-m    3
A16      M602           M602       H807     dec-m    3
A18      G888           G888       H807     dec-m    10
A20      G888           G888       H807     dec-m    10
A21      G888           G888       H807     dec-m    10
A22      M502           M502       H807     dec-m    2
A23      M633           M633       H807     dec-m    2
A24      W023           W023       H807     dec-m    12
A25      M916           M916       H807     dec-m    12
A26      M916           M916       H807     dec-m    12
AB01     G821           G821       H807-2   dec-m    10
AB19     W032           W032       H807-2   dec-m    10
B02      M623           M623       H807     dec-m    11
B03      M623           M623       H807     dec-m    11
B04      M623           M623       H807     dec-m    11
B05      M623           M623       H807     dec-m    11
B06      M111           M111       H807     dec-m    1
B07      M207           M207       H807     dec-m    2
B08      M113           M113       H807     dec-m    1
B09      M206           M206X      H807     dec-m    8
B10      M627           M627       H807     dec-m    1
B11      M115           M115       H807     dec-m    2
B12      M117           M117       H807     dec-m    4
B13      M206           M206X      H807     dec-m    4
B14      M206           M206X      H807     dec-m    2
B15      M113           M113       H807     dec-m    3
B16      M602           M602       H807     dec-m    3
B18      G888           G888       H807     dec-m    10
B20      G888           G888       H807     dec-m    10
B21      G879           G879       H807     dec-m    6
B22      M633           M633       H807     dec-m    2
B23      W005           W005       H807     dec-m    2
C01      M101           M101       H807     dec-m    1
C02      M101           M101-ARRAY H807     dec-m    11
C03      M101           M101-ARRAY H807     dec-m    11
C04      M103           M103       H807     dec-m    1
C05      M103           M103       H807     dec-m    1
C06      M111           M111       H807     dec-m    1
C07      M207           M207       H807     dec-m    2
C08      M121           M121       H807     dec-m    1
C09      M206           M206X      H807     dec-m    8
C10      M121           M121       H807     dec-m    6
C11      M113           M113       H807     dec-m    4
C12      M115           M115       H807     dec-m    3
C13      M111           M111       H807     dec-m    3
C14      M206           M206X      H807     dec-m    3
C15      M113           M113       H807     dec-m    3
C16      M627           M627       H807     dec-m    1
C17      M111           M111       H807     dec-m    1
CD18     M228           M228       H807-2   dec-m    7
D02      M903           M903       H807     dec-m    12
D03      M903           M903       H807     dec-m    12
D04      M903           M903       H807     dec-m    12
D05      M903           M903       H807     dec-m    12
D06      M903           M903       H807     dec-m    12
D07      M161           M161       H807     dec-m    2
D08      M207           M207       H807     dec-m    9
D09      M121           M121       H807     dec-m    2
D10      M119           M119       H807     dec-m    3
D11      M206           M206X      H807     dec-m    1
D12      M627           M627       H807     dec-m    1
D13      M602           M602       H807     dec-m    1
D14      M307           M307       H807     dec-m    3
D15      M401           M401       H807     dec-m    3
D16      M302           M302       H807     dec-m    6
D17      M602           M602       H807     dec-m    1

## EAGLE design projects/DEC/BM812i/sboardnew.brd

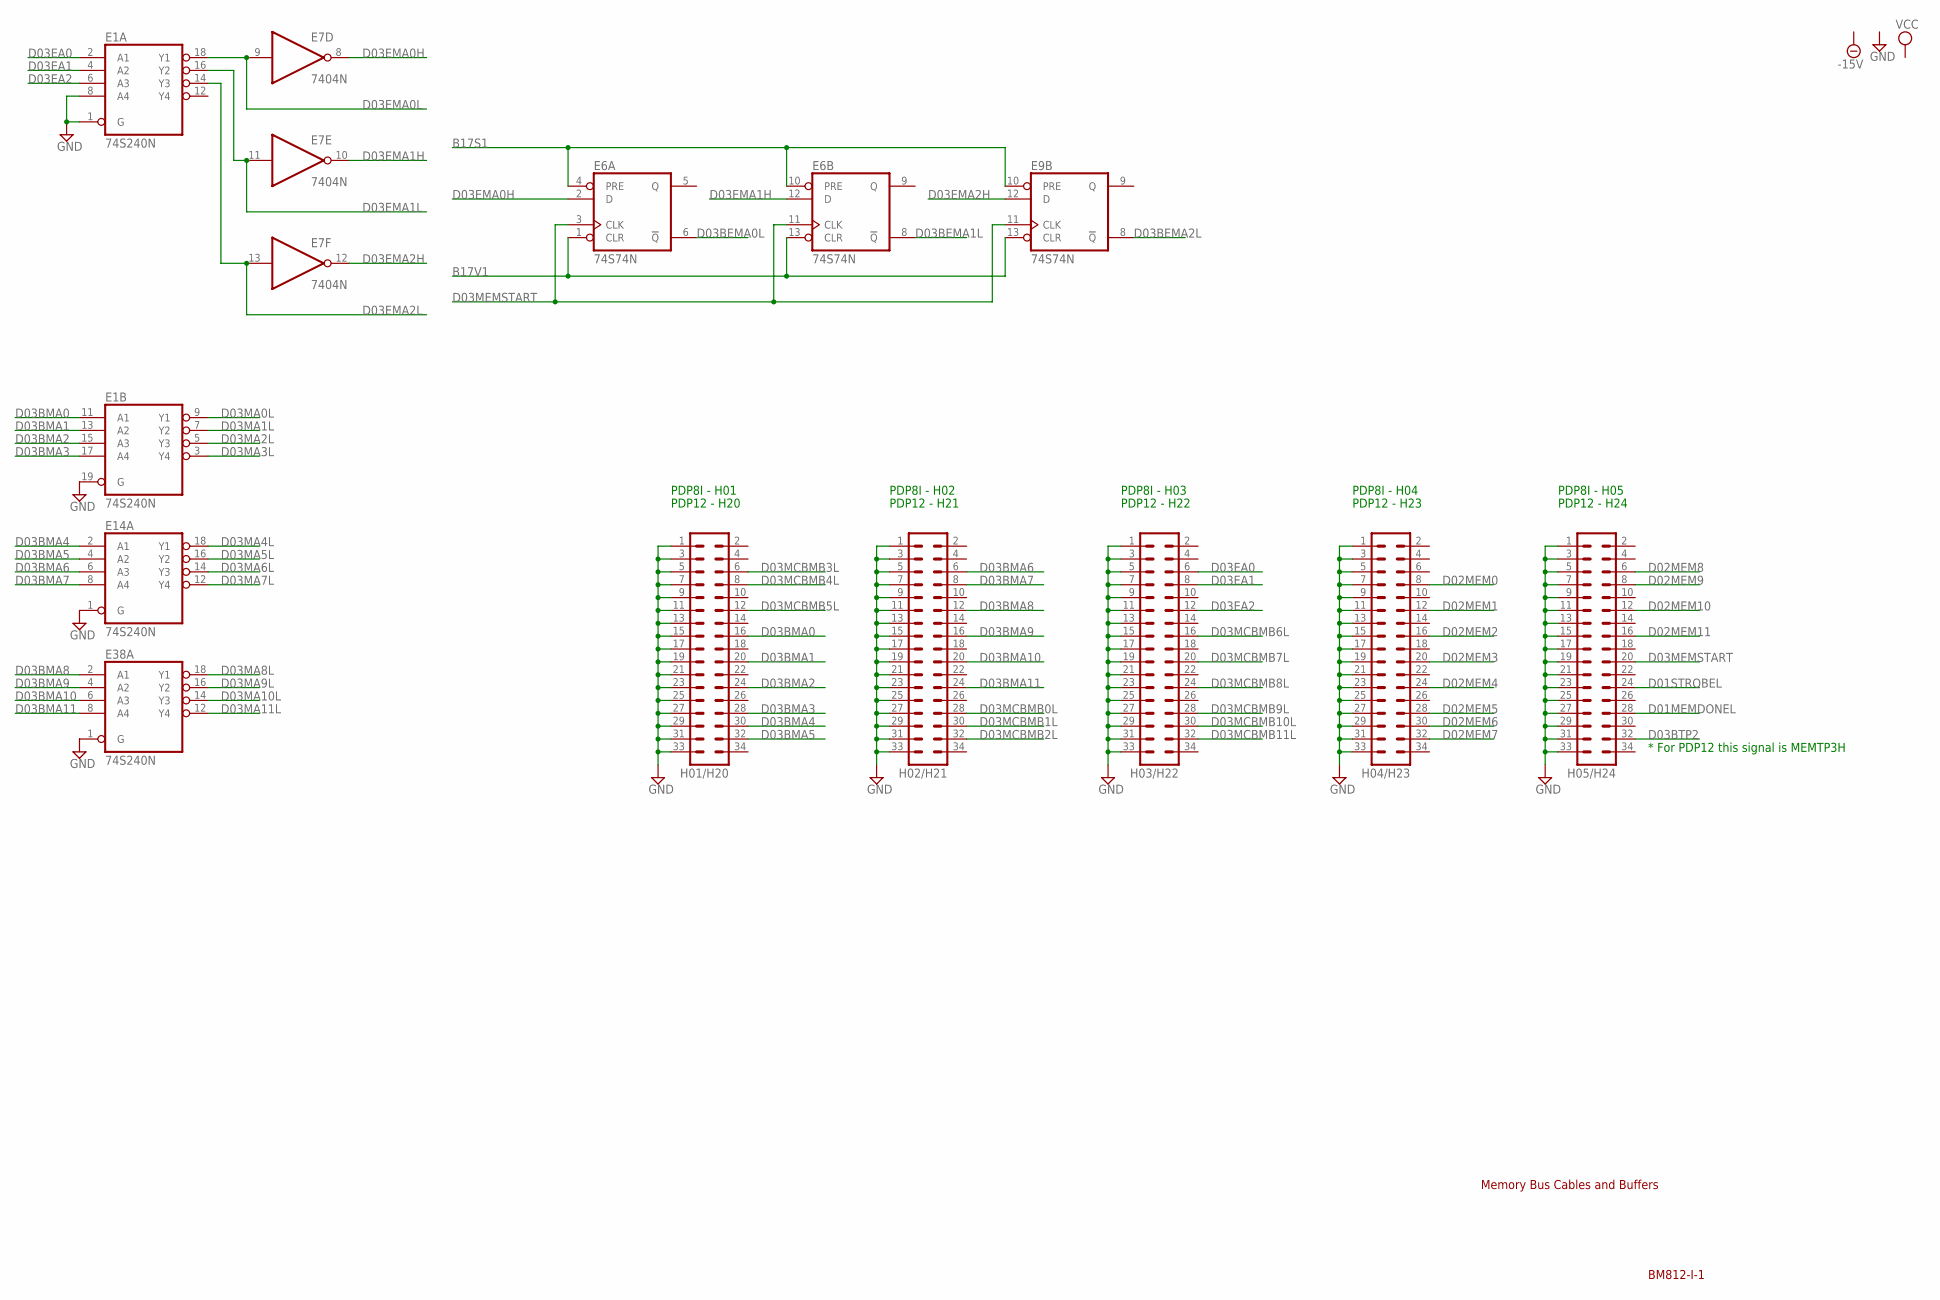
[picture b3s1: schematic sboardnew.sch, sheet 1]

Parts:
E1, E14, E38: 74S240N; DIL20
E6, E9: 74S74N; DIL14
E7: 7404N; DIL14
H01/H20, H02/H21, H03/H22, H04/H23, H05/H24: MA17-2

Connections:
B17S1: E6.4 (PRE), E6.10 (PRE), E9.10 (PRE); also elsewhere on the board
B17V1: E6.1 (CLR), E6.13 (CLR), E9.13 (CLR); also elsewhere on the board
D01MEMDONEL: H05/H24.28; also elsewhere on the board
D01STROBEL: H05/H24.24; also elsewhere on the board
D02MEM0: H04/H23.8; also elsewhere on the board
D02MEM1: H04/H23.12; also elsewhere on the board
D02MEM2: H04/H23.16; also elsewhere on the board
D02MEM3: H04/H23.20; also elsewhere on the board
D02MEM4: H04/H23.24; also elsewhere on the board
D02MEM5: H04/H23.28; also elsewhere on the board
D02MEM6: H04/H23.30; also elsewhere on the board
D02MEM7: H04/H23.32; also elsewhere on the board
D02MEM8: H05/H24.6; also elsewhere on the board
D02MEM9: H05/H24.8; also elsewhere on the board
D02MEM10: H05/H24.12; also elsewhere on the board
D02MEM11: H05/H24.16; also elsewhere on the board
D03BEMA0L: E6.6 (!Q); also elsewhere on the board
D03BEMA1L: E6.8 (!Q); also elsewhere on the board
D03BEMA2L: E9.8 (!Q); also elsewhere on the board
D03BMA0: E1.11 (A1), H01/H20.16
D03BMA1: E1.13 (A2), H01/H20.20
D03BMA2: E1.15 (A3), H01/H20.24
D03BMA3: E1.17 (A4), H01/H20.28
D03BMA4: E14.2 (A1), H01/H20.30
D03BMA5: E14.4 (A2), H01/H20.32
D03BMA6: E14.6 (A3), H02/H21.6
D03BMA7: E14.8 (A4), H02/H21.8
D03BMA8: E38.2 (A1), H02/H21.12
D03BMA9: E38.4 (A2), H02/H21.16
D03BMA10: E38.6 (A3), H02/H21.20
D03BMA11: E38.8 (A4), H02/H21.24
D03BTP2: H05/H24.32; also elsewhere on the board
D03EA0: E1.2 (A1), H03/H22.6
D03EA1: E1.4 (A2), H03/H22.8
D03EA2: E1.6 (A3), H03/H22.12
D03EMA0H: E6.2 (D), E7.8 (O); also elsewhere on the board
D03EMA0L: E1.18 (Y1), E7.9 (I); also elsewhere on the board
D03EMA1H: E6.12 (D), E7.10 (O); also elsewhere on the board
D03EMA1L: E1.16 (Y2), E7.11 (I); also elsewhere on the board
D03EMA2H: E7.12 (O), E9.12 (D); also elsewhere on the board
D03EMA2L: E1.14 (Y3), E7.13 (I); also elsewhere on the board
D03MA0L: E1.9 (Y1); also elsewhere on the board
D03MA1L: E1.7 (Y2); also elsewhere on the board
D03MA2L: E1.5 (Y3); also elsewhere on the board
D03MA3L: E1.3 (Y4); also elsewhere on the board
D03MA4L: E14.18 (Y1); also elsewhere on the board
D03MA5L: E14.16 (Y2); also elsewhere on the board
D03MA6L: E14.14 (Y3); also elsewhere on the board
D03MA7L: E14.12 (Y4); also elsewhere on the board
D03MA8L: E38.18 (Y1); also elsewhere on the board
D03MA9L: E38.16 (Y2); also elsewhere on the board
D03MA10L: E38.14 (Y3); also elsewhere on the board
D03MA11L: E38.12 (Y4); also elsewhere on the board
D03MCBMB0L: H02/H21.28; also elsewhere on the board
D03MCBMB1L: H02/H21.30; also elsewhere on the board
D03MCBMB2L: H02/H21.32; also elsewhere on the board
D03MCBMB3L: H01/H20.6; also elsewhere on the board
D03MCBMB4L: H01/H20.8; also elsewhere on the board
D03MCBMB5L: H01/H20.12; also elsewhere on the board
D03MCBMB6L: H03/H22.16; also elsewhere on the board
D03MCBMB7L: H03/H22.20; also elsewhere on the board
D03MCBMB8L: H03/H22.24; also elsewhere on the board
D03MCBMB9L: H03/H22.28; also elsewhere on the board
D03MCBMB10L: H03/H22.30; also elsewhere on the board
D03MCBMB11L: H03/H22.32; also elsewhere on the board
D03MEMSTART: E6.3 (CLK), E6.11 (CLK), E9.11 (CLK), H05/H24.20; also elsewhere on the board
GND: E1.1 (G), E1.8 (A4), E1.10 (GND), E1.19 (G), E6.7 (GND), E7.7 (GND), E9.7 (GND), E14.1 (G), E14.10 (GND), E38.1 (G), E38.10 (GND), H01/H20.1, H01/H20.3, H01/H20.5, H01/H20.7, H01/H20.9, H01/H20.11, H01/H20.13, H01/H20.15, H01/H20.17, H01/H20.19, H01/H20.21, H01/H20.23, H01/H20.25, H01/H20.27, H01/H20.29, H01/H20.31, H01/H20.33, H02/H21.1, H02/H21.3, H02/H21.5, H02/H21.7, H02/H21.9, H02/H21.11, H02/H21.13, H02/H21.15, H02/H21.17, H02/H21.19, H02/H21.21, H02/H21.23, H02/H21.25, H02/H21.27, H02/H21.29, H02/H21.31, H02/H21.33, H03/H22.1, H03/H22.3, H03/H22.5, H03/H22.7, H03/H22.9, H03/H22.11, H03/H22.13, H03/H22.15, H03/H22.17, H03/H22.19, H03/H22.21, H03/H22.23, H03/H22.25, H03/H22.27, H03/H22.29, H03/H22.31, H03/H22.33, H04/H23.1, H04/H23.3, H04/H23.5, H04/H23.7, H04/H23.9, H04/H23.11, H04/H23.13, H04/H23.15, H04/H23.17, H04/H23.19, H04/H23.21, H04/H23.23, H04/H23.25, H04/H23.27, H04/H23.29, H04/H23.31, H04/H23.33, H05/H24.1, H05/H24.3, H05/H24.5, H05/H24.7, H05/H24.9, H05/H24.11, H05/H24.13, H05/H24.15, H05/H24.17, H05/H24.19, H05/H24.21, H05/H24.23, H05/H24.25, H05/H24.27, H05/H24.29, H05/H24.31, H05/H24.33; also elsewhere on the board
VCC: E1.20 (VCC), E6.14 (VCC), E7.14 (VCC), E9.14 (VCC), E14.20 (VCC), E38.20 (VCC); also elsewhere on the board

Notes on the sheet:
Memory Bus Cables and Buffers
BM812-I-1
* For PDP12 this signal is MEMTP3H
PDP8I - H01
PDP8I - H02
PDP8I - H03
PDP8I - H04
PDP8I - H05
PDP12 - H20
PDP12 - H21
PDP12 - H22
PDP12 - H23
PDP12 - H24
